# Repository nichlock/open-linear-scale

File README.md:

# Open-Source Capacitive Linear Encoder

This is an open-source capacitive encoder design with hardware, firmware, test data, and design details. This design is still in development. It's targeted towards open-source DRO sensors and digital calipers. The build costs roughly $32 before shipping.

# Overview

| Parameter    | Value            |
| ------------ | ---------------- |
| Encoder Type | Incremental      |
| Method       | Capacitive       |
| Accuracy     | 40µm (1.6 thou)* |
| Output Type  | UART             |

*Measured against a Mitutoyo 543-793B-12 at room temperature. This value is based on the electrical precision and resolution. See [Practical Accuracy Measurements](#practical-accuracy-measurements) for a summary of the measured error.

## Quickstart

1. Order the 4-layer sensor and the reflector ([hardware](hardware/README.md)).
2. [Assemble](mechanical/README.md#bom-and-assembly-instructions).
3. Flash the [firmware](firmware/README.md#building-and-flashing).
4. Apply Kapton for the [0.1mm gap](#mechanical-integration).
5. Set the [trimmer](hardware/README.md#trimmer).
6. Run `LiveView.py` with your serial port, for example `python LiveView.py COM3` ([tests](tests/README.md#ports-and-settings)).

## Why Make This

This sensor came out of a long-running personal project. I started by reverse-engineering digital capacitive calipers. I wanted to publish this working capacitive encoder because I had trouble finding open information about them.

I hope this project is useful to someone, but my real goal was to learn, not to replace existing pro-grade encoders.

## What's Included

This is a capacitive encoder, the same technology found in older pro-grade capacitive linear scales. Today, capacitive encoders are mostly found in hobby-grade digital calipers.

It is also incremental. It measures position precisely within each 5.08mm period, and counts how many periods it has passed through. At power-up it assumes it is at position zero, so it needs zeroing or homing every time it starts.

The design is split into folders by discipline:

- `hardware`: The KiCad PCB designs.
- `firmware`: Firmware for the sensor PCB.
- `mechanical`: Mechanical test fixtures.
- `tests`: Test and analysis scripts.

Each folder has its own README with deeper dives into its topics.

## How it Works

The encoder has two parts: a **sensor PCB** that moves along the axis, and a passive **reflector PCB** fixed along its length. They do not touch. The copper faces sit about 0.1mm apart.

| Sensor PCB Bottom                                                                  | Sensor PCB Top                                                                             |
| ---------------------------------------------------------------------------------- | ------------------------------------------------------------------------------------------ |
|  |  |

The sensor PCB has a sensing grid of 8 repeating transmit antennas, which I've called **emitters**. It also has an RX antenna, which feeds a charge integrator and an anti-alias filter. The analog hardware is fully integrated within the STM32L4. See [Analog Frontend](#analog-frontend) for more design information.

| Reflector PCB Top                                                             |
| ----------------------------------------------------------------------------- |
|  |

The reflector has a row of T-shaped copper pads. They "reflect" the capacitance of four of the eight repeating emitters into the RX antenna.

The position of the reflector relative to the sensor decides which emitters couple, and how strongly.

**Measurement cycle.** The STM32 steps its 8 emitter pins through a fixed 16-step pattern. At each step, some emitters switch low-to-high or high-to-low. Charge couples through the reflector into the RX antenna. A charge integrator captures it, a low-pass filter smooths it, and the ADC oversamples it. The steps run at 16kHz, so a full sequence completes at 1kHz.

**Position estimate.** Each sequence gives a position within one period. The [Functional Description](#functional-description) explains how. Unwrapping successive estimates gives a continuous position. For this to work, the sensor can't be moving too fast for the algorithm to track. Conservatively, the maximum speed might be 0.6m/s, although I have not tested this.

**Output.** The sensor outputs a hex-equivalent floating point value over UART at 460800 baud, every millisecond. The script `tests/LiveView.py` plots a position on the host. The sensor can also output other formats and debugging information.

## Status and Limitations

A capacitive encoder is sensitive to liquids between the boards. At these accuracies, thermal expansion over long distances also matters. Plan for both if you would like to integrate with this.

When I started, I hoped for 10µm electrical accuracy. My first revision was about 0.5mm. I'm still working towards 10µm, along with a few other features:

- Automatic electrical calibration.
- Temperature compensation.
- Less reliance on the STM32L4, which is getting harder to source. The plan is a more standard STM32 with a discrete analog frontend.
- Improvements to the layout and mechanical design.
- Absolute position sensing.

I'd welcome help with these! Especially the mechanical design, which is far outside my expertise. See [CONTRIBUTING.md](CONTRIBUTING.md) for how to get involved.

# Practical Accuracy Measurements

I give an accuracy 'rating' of 40µm. I measured the error against a Mitutoyo 543-793B-12 digital indicator. The [mechanical README](mechanical/README.md) has more detail on the setup. I read the accuracy figure visually from the plots and rounded it up conservatively. My overall design isn't mature enough for a true tolerance stackup yet. The [tests README](tests/README.md#accuracy-analysis) has an in-depth analysis. Here is a summary of the major error sources:
- **Systematic error** is dominated by a periodic error that correlates with position. It's the large triangular deviations around 1–3mm and 7–9mm. There is also a smaller error that repeats every emitter (0.635mm) and drift that most likely comes from my test assembly.
- **Noise** is smaller than the systematic error. It is mostly white noise, plus a low-frequency resonance of my 3D printer.

# Functional Description

## Measurement Cycle

The diagram below gives an overview of each step of a position measurement:

The emitters switch at 16kHz, stepping through 16 states. After all 16, the measurements go through the position algorithm. 

The timing diagram below shows an example of the 16 states:

The integrator output always has roughly the shape shown in the plot. As the position changes, it appears phase-shifted relative to the zero position.

# The Position Algorithm

This section builds up the reasoning behind each step of the position algorithm. The final steps are best read in [the code](firmware/src/sensor-math.cpp).

The sensor measures how the reflector lines up with the emitters, which are coupled to the RX antenna through capacitance.

Consider a single emitter. If the reflector overlaps it, there is a strong capacitance from the emitter to the RX antenna. If not, there is no extra capacitance. When an overlapped emitter switches from low to high, the RX antenna sees a pulse.

When the emitter is only partly overlapped, the coupling falls roughly linearly with movement.

With more emitters, the effect adds up linearly. By driving the first four emitters low-to-high and the next four high-to-low, the size of the pulse tells us where the reflector is.

In the plot, "coupling" goes negative. That means the reflector is aligned with the emitters making the negative transition, not that the capacitance is negative.

That is technically enough to get a position, but there are two problems:

1. We don't know the pulse size of a fully overlapped emitter, and it changes over time.
2. Because the pattern repeats, each pulse size matches two possible positions. In the plot below, a measurement could mean 3.1 or 4.9, and we can't tell which.

Taking more measurements solves both problems. Instead of sampling one location, we "slide" the pattern across all eight emitters, giving eight pulse sizes. The second four are the negatives of the first four, so they combine into four pulses.

Each of the four pulses gives two candidate positions, and we could pick the one they all agree on. Near the edges, though, noise makes that choice unreliable. The resulting error is larger than the noise itself, and it is nonlinear.

Finding the zero crossing of the line through the pulses avoids the nonlinearity and gives lower noise. Depending on the convention, there may be a constant offset (-2 in the plot below).

A few practical problems remain:

1. The samples don't always cross zero.
2. A digital line can't repeatedly step in the same direction.
3. The emitters and reflector pads need clearance between them.

## Pulse Sequences That Don't Cross Zero

The signal is periodic, so we can wrap the first pulse around after the last one and interpolate there. A virtual sample at location 4, equal to the negative of location 0, always creates a zero crossing if there wasn't one already.

## Repeated Positive/Negative Pulses

True sliding pulses would need the emitter voltages to keep stepping up. A digital line can only go low-to-high once; it has to go high-to-low before it can rise again.

My solution is a partial transient between the full ones, which flips three emitters in each half. Why not flip just one? Because this extra transient can also give a position. Three emitters make a larger signal, and one that works with the same interpolation method.

The three-emitter transients give a pulse sequence much like the four-emitter one. They only reach 3/4 of the magnitude, but within that range the signal looks the same, so the same zero-crossing method gives a position.

That estimate is shifted ahead by 0.5 emitters, so adding 0.5 brings it into line.

## Non-Zero Spacing

The emitters and reflector pads need electrical clearance between them.

A naive parallel-plate model would say the signal doesn't change while an edge passes over this gap, so positions inside it can't be recovered.

In reality, as long as the gap is small compared to the copper width, fringing at the copper edges adds significant capacitance. The transition is smooth, but unfortunately not a straight line.

Separating the sensor and reflector reduces the problem. I usually use about 0.1mm. The plot below shows the error that remains, despite fringing, when the PCBs touch.

## Combined Symmetric Measurements

The design takes advantage of a few symmetries in the emitter pattern.

Of the 8 emitters, the second half is always driven as the inverse of the first half. The emitter states are states in time, but what we measure is the difference from one state to the next. The [firmware README](firmware/README.md#emitter-states-and-lanes) shows how this maps to the code.

The second half of the sequence is also an inverted repeat of the first half. Each transient in the second half is the negative of its partner in the first half, so subtracting the two doubles the signal.

The transients also interleave. They alternate between flipping three emitters in each half and flipping four. I call these two interleaved sets **lanes**, which leaves two lanes of four values each. Most of my analysis only considers four emitters and four transients, because that describes most of the signal.

Each lane gives one zero-crossing estimate with its own offset. After applying the offsets, the estimates are averaged.

The offsets are relative. It doesn't matter which lane is treated as the reference, as long as the difference between them is consistent.

# Analog Frontend

The RX antenna receives a voltage pulse. Its height depends on the capacitive coupling, and how long it lasts depends on resistive leakage.

You can sample that pulse directly with the ADC, but only for low accuracy. It needs very short sample windows and can't be anti-alias filtered well, so it picks up a lot of noise.

Instead, the RX antenna feeds a **charge integrator**. The ratio of its two capacitors sets its gain. The integrator turns the short pulse into a held step. The ADC can then oversample over a long window, which improves SNR.

An **anti-alias filter** follows the integrator. It removes the above-Nyquist electrical noise that the integrator passes through.

The firmware measures the change from one integrator state to the next, so the integrator never needs a reset.

The [hardware README](hardware/README.md#sensor-analog-frontend-design-details) covers the design in more detail with rationale.

# Mechanical Integration

The sensor and reflector PCBs are both aligned with 3mm pins and mounted with M3 fasteners.

The sensor and reflector need a gap between them. I aim for 0.1mm. Without it, the signal is larger, but [physical nonlinearities](#non-zero-spacing) wipe out any SNR benefit.

I haven't measured how sensitive the sensor is to a gap, sideways offset or tilt. The effect doesn't seem large, and in theory the design should tolerate all three reasonably well.

I tried a 3D printed shim to set the gap, but two layers of Kapton tape turned out to be much easier and more accurate.

The [mechanical README](mechanical/README.md) covers a typical mechanical stackup and the test fixtures.

# License

This project uses two licenses:

| Folders                        | License                              |
| ------------------------------ | ------------------------------------ |
| `hardware/`, `mechanical/`     | [CERN-OHL-P-2.0](LICENSE-CERN-OHL-P) |
| `firmware/`, `tests/`, `docs/` | [MIT](LICENSE-MIT)                   |

Both are permissive. You can use, modify, make and sell the designs and code, including commercially, as long as you keep the copyright and license notices.

Some files are covered by their own licenses instead:

- `firmware/src/cube-mx-autogen/` contains files generated by STM32CubeMX, © STMicroelectronics. They are under BSD-3-Clause or Apache-2.0, depending on the file. See the [license file in that folder](firmware/src/cube-mx-autogen/LICENSE.md).

See [LICENSE](LICENSE) for the summary.

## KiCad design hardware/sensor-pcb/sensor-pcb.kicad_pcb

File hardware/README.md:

# Hardware

All boards are KiCad 9 projects. Their outputs (fabrication, assembly, BOM and STEP files) are generated by each project's `exports.kicad_jobset` and are not committed to the repository. The [Hardware workflow](../.github/workflows/hardware.yml) builds them on GitHub and publishes them as release files.

The links below point to the [development release](https://github.com/nichlock/open-linear-scale/releases/tag/development). It is rebuilt from the latest commit on `main`, so it is only the latest state of the design. It has not been checked as a whole or built as hardware. Versioned releases will be listed on the [releases page](https://github.com/nichlock/open-linear-scale/releases).

## Sensor PCB

This is the active board which runs the firmware. 

The bill of materials does not include a programming connector. 

There is not a programming connector footprint on the board. Instead there are pads for a Tag-Connect bed-of-nails style connector. I used the TC2030-CTX with my JLink EDU mini. More details on flashing are in the [firmware readme](../firmware/README.md#building-and-flashing).

You will also need a UART adapter. For debugging, I use this [DTECH USB to TTL Adapter](https://www.amazon.com/dp/B0DSS4Y8R5) part off amazon as the debug UART adapter and 5V power supply.

The power input accepts 5V. It goes directly to two AP7354 LDOs and nowhere else. I have not done formal WCA or testing, but an input of 4.5~5.5V should pose no issues. The sensor draws peaks of about 25mA.

You can find the latest gerber and STEP files in the [releases](https://github.com/nichlock/open-linear-scale/releases).

| Parameter      | Value           |
| -------------- | --------------- |
| Layer count    | 4               |
| Thickness      | 1.6mm           |
| Substrate      | FR-4            |
| Surface Finish | HASL acceptable |

| Layer      | Purpose                                                         |
| ---------- | --------------------------------------------------------------- |
| Top        | Signals and components                                          |
| Internal 1 | GND (shield from top)                                           |
| Internal 2 | GND (with an opening to reduce capacitance to the receiver pad) |
| Bottom     | Sensor Grid                                                     |

An I2C STEMMA-style header was designed in but DNP'd from the BOM. At time of writing I have not tested I2C at all.

J2 (a 5-pin JST PH) is the only connector that is needed for typical operation. Connect a 5V supply and a UART device. Right now, PC12 isn't used. It might be used later as a part of an SSI output.

> Side note: do you actually need four layers? I tested this. I first designed this board to work with two layers, then at the end I added two more internal ground planes. I ordered a 2- and 4- layer variant. There is some extra inaccuracy caused by asymmetric coupling from the emitters to the RX pad. It results in a higher inaccuracy on the order of 0.1mm. The 4-layer board has ground planes which fix this. In theory electrical calibration could fix this too, but I haven't gotten to calibration at time of writing.

## Reflector PCB

This PCB is fully passive and has no components. It only serves to provide the "T" pattern as detailed in the main README. There is no schematic or BOM.

This was named the "small" variant. A larger variant was designed first but has never been tested. I chose to keep only one length at time of initial release. See [Making a Longer Reflector](#making-a-longer-reflector) if you're interested in a longer version.

This PCB is a two layer stackup. Copper is placed on the "wrong" side of the board (the side that faces away from the sensor PCB). That copper was added to mitigate warping. *(When I built up an old revision of this encoder, I ordered the reflectors with a 0.8mm fab, and it was very warped.)*

- [Fabrication Files](https://github.com/nichlock/open-linear-scale/releases/download/development/reflector-pcb-sm-fabrication.zip) (development release)
- [STEP Model](https://github.com/nichlock/open-linear-scale/releases/download/development/reflector-pcb-sm.step) (development release)

| Parameter      | Value                        |
| -------------- | ---------------------------- |
| Layer count    | 2                            |
| Thickness      | 1.6mm                        |
| Substrate      | FR-4                         |
| Surface Finish | Not applicable (no openings) |

# Making a Longer Reflector

The reflector PCB is a repetition of two pads every 200mil.

You can make a longer reflector by simply copy/pasting however many of these that you need in a row on a 200mil grid.

After that, move the mechanical mounting features.

Note that the usable travel is `((number of repetitions) * 0.2") - (1.2")` (excluding mechanical mounting space). The 1.2" is the width of the sensor grid. That grid needs to be fully covered for the sensor to work reliably.

# Sensor Analog Frontend Design Details

We receive a voltage pulse on the receiving antenna. The height of the pulse depends on the capacitive coupling, and the length of time that the pulse lasts depends on the resistive leakage.

## ADC-Only Samples

One way to measure the RX input is to put it directly into an ADC. At first, this was all I did.

This method works well enough for low-accuracy. There are two problems:
1. The ADC needs to use very small sample windows, making it vulnerable to noise.
2. The signal can't be conditioned easily. The shape of the pulse is also not conducive to anti-alias filtering. As a consequence, I was getting massive problems with above-Nyquist electrical noise while testing near my 3D printer.

## Charge Integrator

A major improvement to this design was the charge integrator. This allows us to widen the ADC window all the way to a zeroth order hold.

The charge integrator creates a gain that is the ratio of the two capacitors. I used a trimmer capacitor for adjustable gain.

Another major benefit is that we can now oversample the ADC over a long window of time. That alone gives a better SNR.

Although this did improve the SNR against white noise, it doesn't solve the entire anti-aliasing problem. Most noise still goes right through the charge integrator. My 3D printer's major noise component comes in 23kHz, compared to the 16kHz step rate (this was before I added any shielding). So an anti-alias filter is added on. The filter slews the signal significantly, but it results in a much better SNR in the presence of above-Nyquist electrical noise.

The integrator is leaky (100MΩ resistor) in order to prevent DC drifting.

The firmware measures the difference between one integrator state and the next, not the magnitude of one pulse against vref. That means we don't have to worry about resetting the integrator.

## VREF

Vref is chosen at 50% VDDA, or 1.65V. It's generated by a DAC. There could be benefits to tuning VREF live since there seems to be asymmetry in the I/O leakage, pulling the average DC value on the RX node away from 50% VCC. That would give more budget for a higher input gain. This isn't a major contributor to accuracy issues so I don't do it right now.

## Trimmer

The easiest way to set the trimmer is to twist it while monitoring the integrator output on an oscilloscope. I also do it by using the LiveView test script, but that can be a little cumbersome due to delays in the plotting.

The trimmer I specified only goes down to 4.5pF. It gained the capacitive pulse up to 1Vpp. I would like a higher magnitude to help reduce the impact of the white noise at the ADC input, although that is scope for future work.

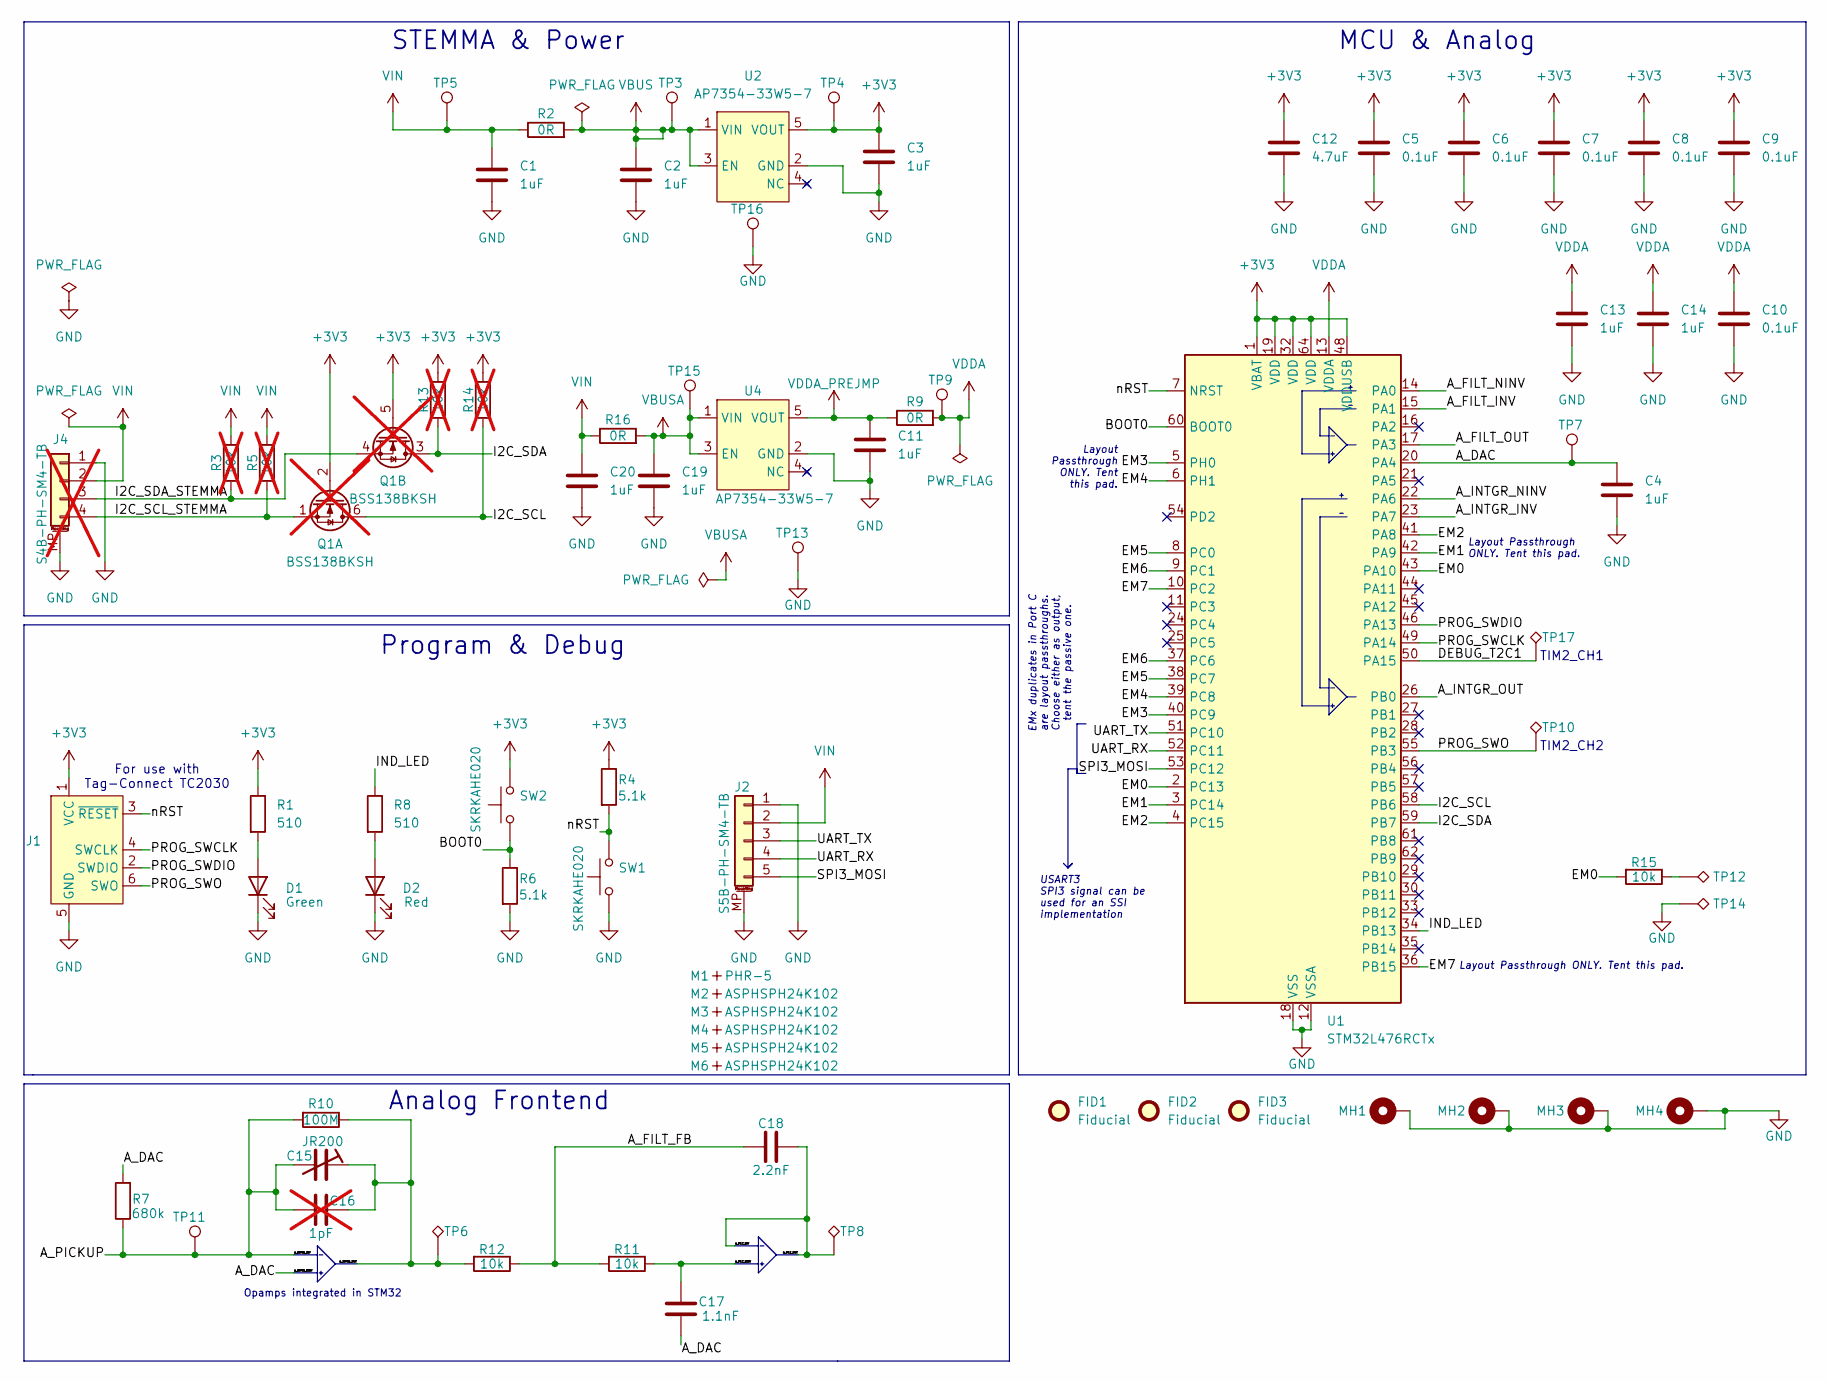
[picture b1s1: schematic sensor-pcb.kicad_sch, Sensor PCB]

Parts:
C1, C2, C3, C4, C11, C13, C14, C19, C20: 1uF; C_0603_1608Metric
C5, C6, C7, C8, C9, C10: 0.1uF; C_0402_1005Metric
C12: 4.7uF; C_0805_2012Metric
C15: JR200; JRx-trimmer
C16: 1pF; C_0402_1005Metric_Pad0.74x0.62mm_HandSolder; not fitted
C17: 1.1nF; C_0603_1608Metric
C18: 2.2nF; C_0603_1608Metric
D1: APT3216LZGCK; LED_1206_3216Metric
D2: APT3216LSECK/J3-PRV; LED_1206_3216Metric
FID1, FID2, FID3: Fiducial; Fiducial_0.5mm_Mask1mm
J1: Conn_ARM_SWD_TagConnect_TC2030; Tag-Connect_TC2030-IDC-FP_2x03_P1.27mm_Vertical
J2: S5B-PH-SM4-TB; JST_PH_S5B-PH-SM4-TB_1x05-1MP_P2.00mm_Horizontal
J4: S4B-PH-SM4-TB; JST_PH_S4B-PH-SM4-TB_1x04-1MP_P2.00mm_Horizontal; not fitted
M1: PHR-5
M2, M3, M4, M5, M6: ASPHSPH24K102
MH1, MH2, MH3, MH4: M3; MountingHole_3.2mm_M3_Pad_Via
Q1: BSS138BKSH; SOT-363_SC-70-6; not fitted
R1, R8: 510; R_0603_1608Metric
R2, R9, R16: 0R; R_0603_1608Metric
R3, R5, R13, R14: 10k; R_0603_1608Metric; not fitted
R4, R6: 5.1k; R_0603_1608Metric
R7: 680k; R_0603_1608Metric
R10: 100M; R_0603_1608Metric
R11, R12, R15: 10k; R_0603_1608Metric
SW1, SW2: SKRKAHE020; SW_Push_SPST_NO_Alps_SKRK
TP3, TP4, TP5, TP7, TP9, TP11, TP13, TP15, TP16: TestPoint; TestPoint_Pad_D1.0mm
TP6, TP8, TP10, TP12, TP14, TP17: TP_Keystone_5015; TestPoint_Keystone_5015_Micro_Mini
U1: STM32L476RCTx; LQFP-64_10x10mm_P0.5mm
U2, U4: AP7354-33W5-7; SOT-23-5_HandSoldering

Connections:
+3V3: C3.1, C5.1, C6.1, C7.1, C8.1, C9.1, C12.1, J1.1 (VCC), Q1.2 (G), Q1.5 (G), R1.1, R4.1, R13.1, R14.1, SW2.2, TP4.1, U1.1 (VBAT), U1.19 (VDD), U1.32 (VDD), U1.48 (VDDUSB), U1.64 (VDD), U2.5 (VOUT)
/A_DAC: C4.1, C17.2, R7.2, TP7.1, U1.20 (PA4), U1.22 (PA6)
/A_FILT_FB: C18.2, R11.2, R12.1
/A_FILT_INV: C18.1, TP8.1, U1.15 (PA1), U1.17 (PA3)
/A_FILT_NINV: C17.1, R11.1, U1.14 (PA0)
/A_INTGR_INV: C15.2, C16.1, R7.1, R10.2, TP11.1, U1.23 (PA7)
/A_INTGR_OUT: C15.1, C16.2, R10.1, R12.2, TP6.1, U1.26 (PB0)
/BOOT0: R6.1, SW2.1, U1.60 (BOOT0)
/DEBUG_T2C1: TP17.1, U1.50 (PA15)
/EM0: R15.2, U1.2 (PC13), U1.43 (PA10)
/EM1: U1.3 (PC14), U1.42 (PA9)
/EM2: U1.4 (PC15), U1.41 (PA8)
/EM3: U1.5 (PH0), U1.40 (PC9)
/EM4: U1.6 (PH1), U1.39 (PC8)
/EM5: U1.8 (PC0), U1.38 (PC7)
/EM6: U1.9 (PC1), U1.37 (PC6)
/EM7: U1.10 (PC2), U1.36 (PB15)
/I2C_SCL: Q1.6 (D), R14.2, U1.58 (PB6)
/I2C_SCL_STEMMA: J4.4, Q1.1 (S), R5.2
/I2C_SDA: Q1.3 (D), R13.2, U1.59 (PB7)
/I2C_SDA_STEMMA: J4.3, Q1.4 (S), R3.2
/IND_LED: R8.1, U1.34 (PB13)
/PROG_SWCLK: J1.4 (SWCLK), U1.49 (PA14)
/PROG_SWDIO: J1.2 (SWDIO), U1.46 (PA13)
/PROG_SWO: J1.6 (SWO), TP10.1, U1.55 (PB3)
/SPI3_MOSI: J2.5, U1.53 (PC12)
/UART_RX: J2.4, U1.52 (PC11)
/UART_TX: J2.3, U1.51 (PC10)
/nRST: J1.3 (~RESET), R4.2, SW1.2, U1.7 (NRST)
GND: C1.2, C2.2, C3.2, C4.2, C5.2, C6.2, C7.2, C8.2, C9.2, C10.2, C11.2, C12.2, C13.2, C14.2, C19.2, C20.2, D1.1 (K), D2.1 (K), J1.5 (GND), J2.1, J2.MP (MountPin), J4.1, J4.MP (MountPin), MH1.1, MH2.1, MH3.1, MH4.1, R6.2, SW1.1, TP13.1, TP14.1, TP16.1, U1.12 (VSSA), U1.18 (VSS), U1.31 (VSS), U1.47 (VSS), U1.63 (VSS), U2.2 (GND), U4.2 (GND)
unnamed: D1.2 (A), R1.2
unnamed: D2.2 (A), R8.2
unnamed: R15.1, TP12.1
VBUS: C2.1, R2.2, TP3.1, U2.1 (VIN), U2.3 (EN)
VBUSA: C19.1, R16.2, TP15.1, U4.1 (VIN), U4.3 (EN)
VDDA: C10.1, C13.1, C14.1, R9.2, TP9.1, U1.13 (VDDA)
VDDA_PREJMP: C11.1, R9.1, U4.5 (VOUT)
VIN: C1.1, C20.1, J2.2, J4.2, R2.1, R3.1, R5.1, R16.1, TP5.1

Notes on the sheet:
TIM2_CH2
Opamps integrated in STM32
STEMMA & Power
MCU & Analog
Analog Frontend
EMx duplicates in Port C are layout passthroughs. Choose either as output, tent the passive one.
USART3 SPI3 signal can be used for an SSI implementation
Layout Passthrough ONLY. Tent this pad.
Layout Passthrough ONLY. Tent this pad.
Layout Passthrough ONLY. Tent this pad.
Program & Debug
TIM2_CH1
For use with Tag-Connect TC2030

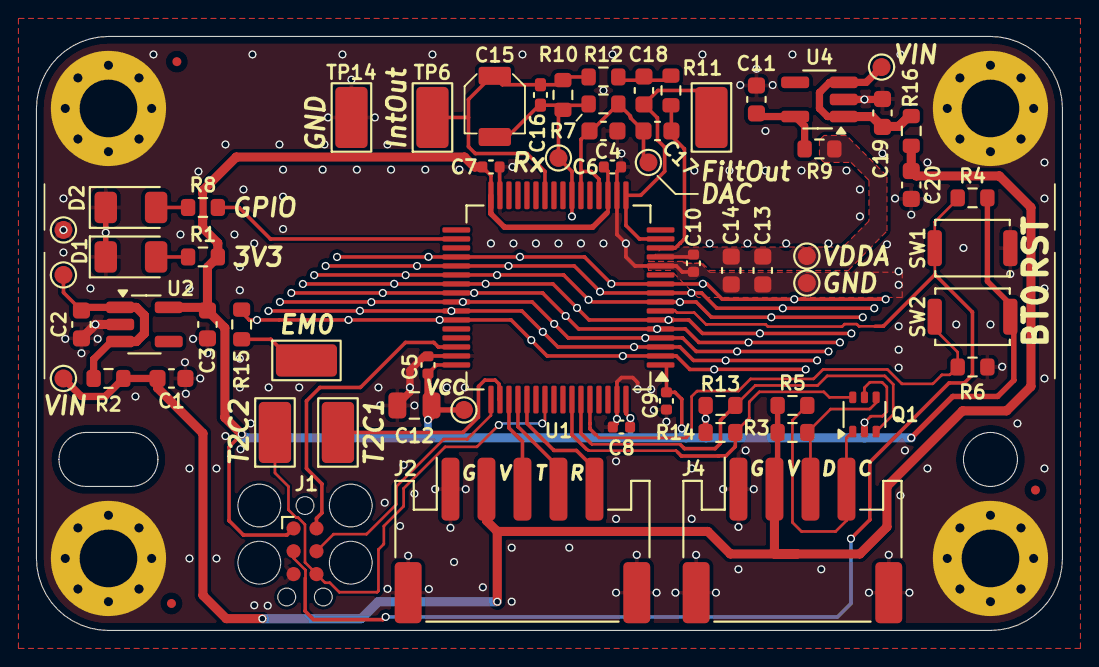
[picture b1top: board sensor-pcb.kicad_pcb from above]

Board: 4 copper layers, 57.0 x 33.0 mm, 69 parts (0 on the bottom side), 38 nets.

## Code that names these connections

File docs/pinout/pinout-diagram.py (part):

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LABELS = [
    # Right: analog test points and the gain trimmer
    ("TP14", "1", "R", [], (RIGHT_X, None), [("GND", "name"), ("GND", "gnd")]),
    ("TP6", "1", "R", [], (RIGHT_X, None), [("IntOut", "name"), ("Integrator out", "other"), ("PB0", "mcu")]),
    ("C15", None, "R", [], (RIGHT_X, None), [("C15", "name"), ("Gain trimmer", "other")]),
    ("TP11", "1", "R", [], (RIGHT_X, None), [("Rx", "name"), ("RX antenna", "other"), ("PA7", "mcu")]),
    ("TP7", "1", "R", [], (RIGHT_X, None), [("DAC", "name"), ("Bias (VREF)", "other"), ("PA4", "mcu")]),
    ("TP8", "1", "R", [], (RIGHT_X, None), [("FiltOut", "name"), ("Filter out", "other"), ("PA3", "mcu")]),
    ("TP9", "1", "R", [], (RIGHT_X, None), [("VDDA", "name"), ("Analog supply", "power")]),
    ("TP13", "1", "R", [(None, 16.4)], (RIGHT_X, 16.4), [("GND", "name"), ("GND", "gnd")]),
    # Top: LEDs
    ("D2", None, "T", [], (None, -30.6), [("GPIO", "name"), ("Status LED", "other"), ("PB13", "mcu")]),
    ("D1", None, "T", [], (None, -32.7), [("3V3", "name"), ("Power LED", "other")]),
    # Bottom: buttons
    ("SW1", None, "B", [], (None, 30.6), [("RST", "name"), ("NRST", "other")]),
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    # Left: J2 main connector
    ("J2", "1", "L", [], (LEFT_X, None), [("GND", "gnd"), ("1", "name")]),
    ("J2", "2", "L", [], (LEFT_X, None), [("VIN", "power"), ("2", "name")]),
    ("J2", "3", "L", [], (LEFT_X, None), [("PC10", "mcu"), ("UART TX", "comms"), ("3", "name")]),
    ("J2", "4", "L", [], (LEFT_X, None), [("PC11", "mcu"), ("UART RX", "comms"), ("4", "name")]),
    ("J2", "5", "L", [], (LEFT_X, None), [("PC12", "mcu"), ("Unused", "dnp"), ("5", "name")]),
    # Left: J4, not fitted
    ("J4", "1", "L", [], (LEFT_X, None), [("GND", "dnp"), ("1", "dnp")]),
    ("J4", "2", "L", [], (LEFT_X, None), [("VIN", "dnp"), ("2", "dnp")]),
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J1_TABLE_CENTRE_Y = -15.0
J1_ROWS = [
    ("1", [("3V3", "power")]),
    ("2", [("SWDIO", "debug"), ("PA13", "mcu")]),
    ("3", [("NRST", "other")]),
    ("4", [("SWCLK", "debug"), ("PA14", "mcu")]),
    ("5", [("GND", "gnd")]),
    ("6", [("SWO", "debug"), ("PB3", "mcu")]),
]

GROUP_TITLES = [  # (text, x, y, horizontal alignment)
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
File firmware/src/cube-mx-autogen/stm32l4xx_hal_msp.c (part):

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
    __HAL_RCC_GPIOA_CLK_ENABLE();
    /**DAC1 GPIO Configuration
    PA4     ------> DAC1_OUT1
    */
    GPIO_InitStruct.Pin = GPIO_PIN_4;
    GPIO_InitStruct.Mode = GPIO_MODE_ANALOG;
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    __HAL_RCC_DAC1_CLK_DISABLE();

    /**DAC1 GPIO Configuration
    PA4     ------> DAC1_OUT1
    */
    HAL_GPIO_DeInit(GPIOA, GPIO_PIN_4);

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    __HAL_RCC_GPIOA_CLK_ENABLE();
    __HAL_RCC_GPIOB_CLK_ENABLE();
    /**OPAMP2 GPIO Configuration
    PA6     ------> OPAMP2_VINP
    PA7     ------> OPAMP2_VINM
    PB0     ------> OPAMP2_VOUT
    */
    GPIO_InitStruct.Pin = GPIO_PIN_6|GPIO_PIN_7;
    GPIO_InitStruct.Mode = GPIO_MODE_ANALOG;
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
    __HAL_RCC_GPIOA_CLK_ENABLE();
    /**OPAMP1 GPIO Configuration
    PA0     ------> OPAMP1_VINP
    PA1     ------> OPAMP1_VINM
    PA3     ------> OPAMP1_VOUT
    */
    GPIO_InitStruct.Pin = GPIO_PIN_0|GPIO_PIN_1|GPIO_PIN_3;
    GPIO_InitStruct.Mode = GPIO_MODE_ANALOG;
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    __HAL_RCC_OPAMP_CLK_DISABLE();

    /**OPAMP2 GPIO Configuration
    PA6     ------> OPAMP2_VINP
    PA7     ------> OPAMP2_VINM
    PB0     ------> OPAMP2_VOUT
    */
    HAL_GPIO_DeInit(GPIOA, GPIO_PIN_6|GPIO_PIN_7);

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    __HAL_RCC_GPIOA_CLK_ENABLE();
    /**USART2 GPIO Configuration
    PA2     ------> USART2_TX
    PA3     ------> USART2_RX
    */
    GPIO_InitStruct.Pin = GPIO_PIN_2|GPIO_PIN_3;
    GPIO_InitStruct.Mode = GPIO_MODE_AF_PP;
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
    __HAL_RCC_GPIOC_CLK_ENABLE();
    /**USART3 GPIO Configuration
    PC10    ------> USART3_TX
    PC11    ------> USART3_RX
    */
    GPIO_InitStruct.Pin = GPIO_PIN_10|GPIO_PIN_11;
    GPIO_InitStruct.Mode = GPIO_MODE_AF_PP;
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
    /**USART2 GPIO Configuration
    PA2     ------> USART2_TX
    PA3     ------> USART2_RX
    */
    HAL_GPIO_DeInit(GPIOA, GPIO_PIN_2|GPIO_PIN_3);

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

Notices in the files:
firmware/src/cube-mx-autogen/stm32l4xx_hal_msp.c:
Copyright (c) 2023 STMicroelectronics.
All rights reserved.
This software is licensed under terms that can be found in the LICENSE file
